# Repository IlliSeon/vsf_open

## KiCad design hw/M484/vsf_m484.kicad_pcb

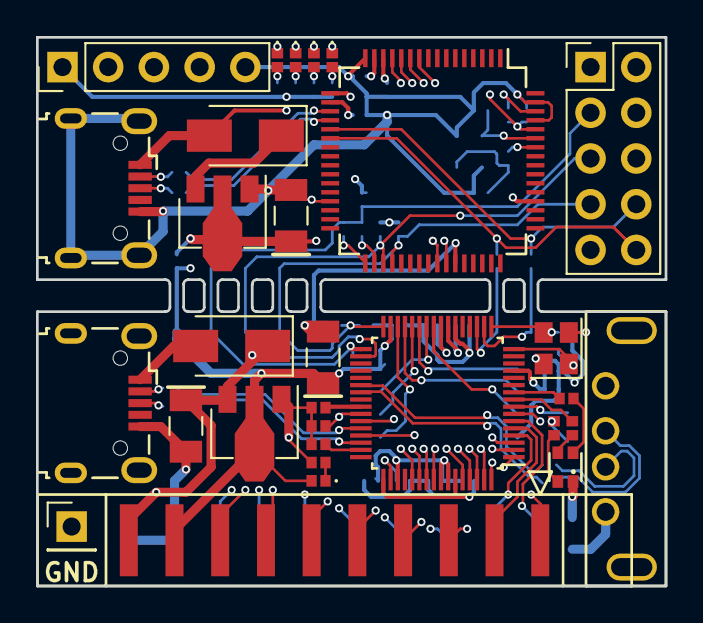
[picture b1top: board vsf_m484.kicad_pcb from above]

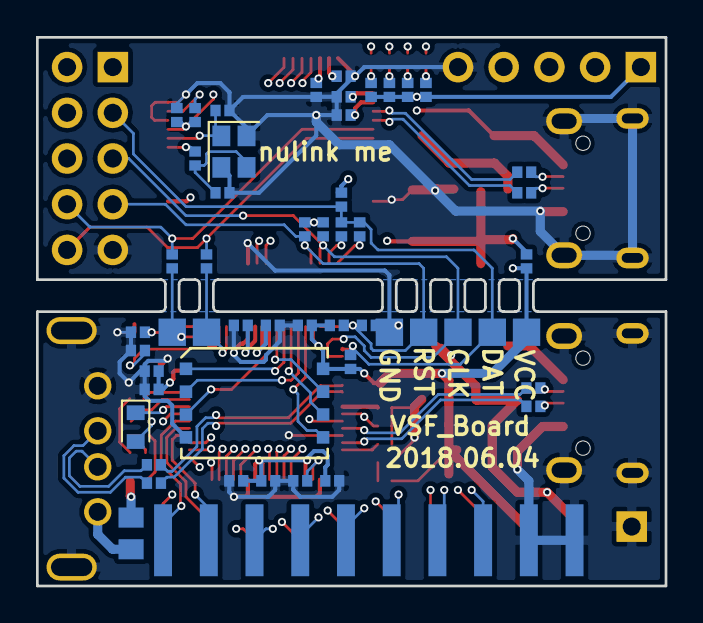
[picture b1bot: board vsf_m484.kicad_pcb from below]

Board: 4 copper layers, 34.9 x 30.5 mm, 82 parts (52 on the bottom side), 81 nets.

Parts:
C0, C1, C25, C26: 20pF; C_0402_1005Metric
C4, C13, C20, C21, C23: 1uF; C_0402_1005Metric
C5, C6: 100uF; C_1206_3216Metric
C7, C8, C9, C15, C16, C22, C24: 0.1uF; C_0402_1005Metric
C14, C17: 4.7uF; C_0402_1005Metric
C18, C19: 2.2uF; C_0402_1005Metric
C27: 10uF; C_0402_1005Metric
C28: 10uF; C_1206_3216Metric
D0, D8: SS14; D_SMA
D1: LED_ARGB; LED_RGB_0603
D2: LED; LED_0402_1005Metric
D3: 1SS400G; D_0603_1608Metric
D4, D6: RED; LED_0402_1005Metric
D5, D7: GREEN; LED_0402_1005Metric
F0: Fuse; Fuse_0805_2012Metric
J1: Conn_02x10_Odd_Even; PinSocket_2x10_P2.54mm_Horizontal_2Layer
J2, J4: USB_OTG; USB_Micro-B_Wuerth_629105150521
J3: USB_A; USB_AF_Sink
J5: Conn_01x05; PinHeader_1x05_P2.54mm_Vertical
J6: Conn_02x05_Odd_Even; PinHeader_2x05_P2.54mm_Vertical
R0: 51K; R_0402_1005Metric
R1, R11: 10K; R_0402_1005Metric
R2, R3, R13: 0; R_0402_1005Metric
R4: 200R %1; R_0402_1005Metric
R5, R6: 33R; R_0402_1005Metric
R7, R8, R9, R10: 1K; R_0402_1005Metric
R12, R14, R15, R16: 33; R_0402_1005Metric
R17, R18, R19, R20: 300; R_0402_1005Metric
R21, R22, R23: 100K; R_0402_1005Metric
R24, R25, R26: NC; R_0402_1005Metric
TP1, TP2, TP3, TP4, TP5, TP6, TP7: TEST; TestPoint_SMD
TP8: TEST; PinHeader_1x01_P2.54mm_Vertical
U0: M4842U_64; LQFP-64_7x7mm_P0.4mm
U1, U4: AP1117-33; SOT-89-3
U2: GD25Q_8P; WSON-8_8x6mm_P1.27mm
U3: NUC120_64; LQFP-64_10x10mm_P0.5mm
Y0, Y2: Crystal_GND24; Crystal_SMD_2520-4Pin_2.5x2.0mm

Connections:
/12M_I: C25.1, U3.59, Y2.1
/12M_O: R12.1, U3.58
/DBG_RXD: R26.2, TP6.1, U0.19
/DBG_TXD: R25.2, TP7.1, U0.18
/DM: R16.1, U3.19
/DP: R15.1, U3.20
/GREEN: D7.1, U3.13
/ICELED: D4.1, U3.10
/ICE_CLK: J5.3, U3.42
/ICE_DAT: J5.2, U3.41
/ISPLED: D5.1, U3.11
/LDO_CAP1: C18.1, U0.24
/LDO_CAP2: C19.1, U0.50
/LEDB: R9.2, U0.10
/LEDG: R8.2, U0.9
/LEDR: D3.1, U0.8
/PB.0: J1.1, U0.7
/PB.1: J1.2, U0.6
/PB.2: J1.3, U0.5
/PB.3: J1.4, U0.4
/PB.4: J1.5, U0.3
/PB.5: J1.6, U0.2
/PB.6: J1.7, U0.1
/PB.7: J1.8, U0.64
/PB.8: J1.9, U0.63
/PB.9: J1.10, U0.62
/PB.10: J1.11, U0.61
/PB.11: J1.12, U0.60
/PB.12: J1.13, U0.56
/PB.13: J1.14, U0.55
/PB.14: J1.15, U0.54
/PB.15: J1.16, U0.53
/RED: D6.1, U3.12
/RST: C27.1, J5.4, R11.2, U3.60
/SPIM_CLK: U0.28, U2.6
/SPIM_D2: U0.25, U2.3
/SPIM_D3: U0.26, U2.7
/SPIM_MISO: U0.29, U2.2
/SPIM_MOSI: U0.30, U2.5
/SPIM_SS: U0.27, U2.1
/SWD_CLK: J6.5, R22.1, TP3.1, U0.34, U3.35
/SWD_DAT: J6.3, R0.2, R13.1, R14.1, R23.1, TP2.1, U0.33
/TICERST: C4.1, J6.7, R1.2, R21.1, TP4.1, U0.32, U3.36
/TICERXD: J6.10, R26.1, U3.22
/TICETXD: J6.8, R25.1, U3.21
/USBD_5V: D0.2, J2.1
/USBD_CAP: C20.1, U0.47
/USBD_DM: R3.1, U0.44
/USBD_DP: R2.1, U0.46
/USBD_VBUS: C5.1, D0.1, D1.1, F0.1, J1.19, U0.43, U1.3
/USBD_VRES: R4.1, U0.41
/USBH_DM: R6.1, U0.38
/USBH_DP: R5.1, U0.39
/VBUS: C23.2, D8.2, J4.1, U3.17
/VCC3: C22.2, C28.1, J5.1, R11.1, R17.2, R18.2, R19.2, R20.2, R21.2, R22.2, R23.2, R24.2, U3.15, U3.52, U3.62, U4.2
/XT_IN: C0.1, U0.16, Y0.1
/XT_OUT: C1.1, U0.17, Y0.3
GND: C0.2, C1.2, C4.2, C5.2, C6.2, C7.2, C8.2, C9.2, C13.2, C14.2, C15.2, C16.2, C17.2, C18.2, C19.2, C20.2, C21.2, C22.1, C23.1, C24.2, C25.2, C26.1, C27.2, C28.2, J1.18, J1.20, J2.5, J2.6, J3.4, J3.5, J4.5, J4.6, J5.5, J6.9, R4.2, R10.1, TP5.1, TP8.1, U0.22, U0.45, U0.49, U0.59, U1.1, U2.4, U3.16, U3.29, U3.43, U3.61, U3.63, U4.1, Y0.2, Y0.4, Y2.2, Y2.4
unnamed: C21.1, U3.14
unnamed: C24.1, U3.18
unnamed: C26.2, R12.2, Y2.3
unnamed: D1.2, R7.1
unnamed: D1.3, R8.1
unnamed: D1.4, R9.1
unnamed: D2.1, R10.2
unnamed: D3.2, R7.2
unnamed: D4.2, R17.1
unnamed: D5.2, R18.1
unnamed: D6.2, R19.1
unnamed: D7.2, R20.1
unnamed: D8.1, U4.3
unnamed: F0.2, J3.1
unnamed: J2.2, R3.2
unnamed: J2.3, R2.2
unnamed: J3.2, R6.2
unnamed: J3.3, R5.2
unnamed: J4.2, R16.2
unnamed: J4.3, R15.2
unnamed: R13.2, U3.34
unnamed: R14.2, U3.33
VCC: C6.1, C7.1, C8.1, C9.1, C13.1, C14.1, C15.1, C16.1, C17.1, D2.2, J1.17, J6.1, R0.1, R1.1, R24.1, TP1.1, U0.13, U0.23, U0.31, U0.42, U0.51, U0.57, U0.58, U1.2, U2.8

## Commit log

2018-04-04 initial version
2018-04-04 add dynpool
2018-04-05 update usart_stream and usart hal
2018-04-07 add fakefat32 demo
2018-04-08 add usart and i2c driver for M480
2018-04-08 vsfhal update
2018-04-08 m480 driver update
2018-04-08 fakefat32 example update
2018-04-08 add usbcdc example
2018-04-09 vsfusbd update
2018-04-09 vsfusbd update: add VSFUSBD_USREVT_IN and VSFUSBD_USREVT_OUT callback
2018-04-09 update uart driver for M480
2018-04-12 update usart_stream
2018-04-12 usart_stream update: add usart_stream_config
2018-04-14 usart_stream update
2018-04-15 m480 usart driver update
2018-04-15 vsfhal update: add rx enable control for usart
2018-04-18 add stepbystep example
2018-04-21 1. add SDIO driver for M480 2. add static in vsfusbh 3. update GPIO and USART driver for M480
2018-06-20 update to the latest open vsf
2018-06-22 add vsfvm_ext_vsfusbh
2018-06-23 bug fix in vsfmc_compiler while processing func->varlist
2018-06-23 m484 hardware update
2018-06-23 add libusb, update 480 project
2018-06-23 add missing vsfvm app files
2018-06-23 bug fix in vsfvm_ext_vsfusbh
2018-06-23 m484 pcb update
2018-06-25 gpio driver update for M480
2018-06-26 add vsfsm_thread support
2018-07-01 sync to the latest private repo
2018-07-01 update example project for usblyzer
2018-07-01 minor fix to previous commit
2018-07-02 vsfvm update, can not distribute event if sm is processing another event
2018-07-02 usbh update, add support to iso transfer
2018-07-03 update vsfusbh driver while processing ep0
2018-07-04 vsfusbh update to optimize iso
2018-07-07 update vsfip and add ipheth driver
2018-07-07 update gd32 usbd driver and usbcdc example
2018-07-08 add rndis driver, not tested
2018-07-08 vsfip_dhcpc optimize to use one buffer
2018-07-09 vsfvm_compiler update: remove bytecode array, add user-defined interface to set/get bytecode
2018-07-09 add project for gd32 vsfvm example
2018-07-09 usblyzer update: callback to user layer for usb actions
2018-07-10 usblyzer update: add output_isbusy callback and VSF_USBLYZER_URB_DELAY configuration
2018-07-10 bug fix in usblyzer if VSFHAL_CFG_USBD_ONNAK_EN is defined
2018-07-10 usblyzer update: reset transact_finished on stall
2018-07-12 vsfvm example update
2018-07-12 usblyzer update: fix zlp error
